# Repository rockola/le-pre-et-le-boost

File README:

# le-pre-et-le-boost
PCB for SMD FET preamp OR booster

* v0.1: initial import, unverified

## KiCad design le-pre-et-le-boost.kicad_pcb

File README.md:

# le-pre-et-le-boost
PCB for SMD FET preamp AND/OR BJT booster

* v0.1: initial import
* v0.2: THT footprints for C1/C2
* v0.3: separate in/out for both sides (for simultaneous use)

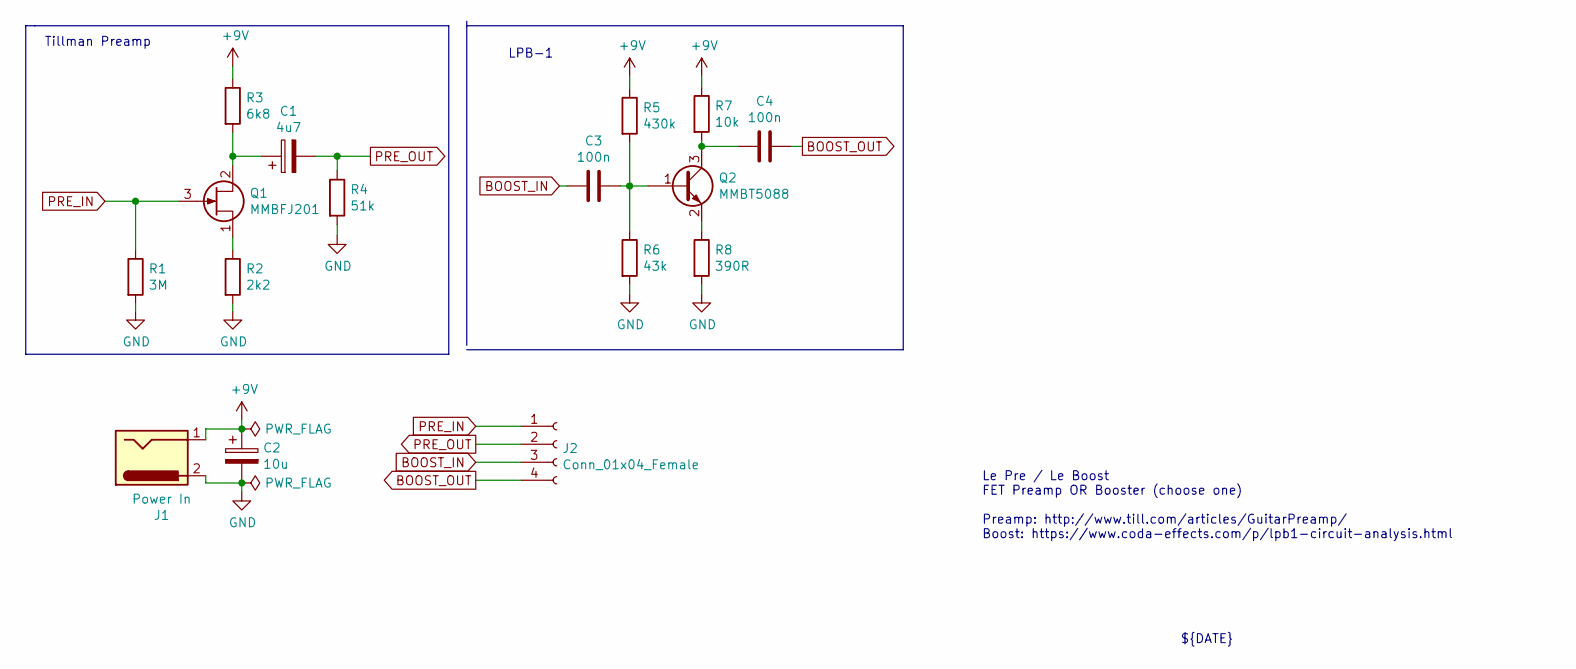
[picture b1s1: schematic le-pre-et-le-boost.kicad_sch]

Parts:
C1: 4u7; CP_D5.0_P2.50
C2: 10u; CP_D5.0_P2.50
C3, C4: 100n; C_0805_2012Metric
J1: Power In; Power_Header_2pin_VERTICAL_ALT
J2: Conn_01x04_Female; Stomp_4pin_ALT2
Q1: MMBFJ201; SOT-23
Q2: MMBT5088; SOT-23
R1: 3M; R_0805_2012Metric
R2: 2k2; R_0805_2012Metric
R3: 6k8; R_0805_2012Metric
R4: 51k; R_0805_2012Metric
R5: 430k; R_0805_2012Metric
R6: 43k; R_0805_2012Metric
R7: 10k; R_0805_2012Metric
R8: 390R; R_0805_2012Metric

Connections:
+9V: C2.1, J1.1, R3.1, R5.1, R7.1
BOOST_IN: C3.1, J2.3
BOOST_OUT: C4.2, J2.4
GND: C2.2, J1.2, R1.2, R2.2, R4.2, R6.2, R8.2
unnamed: C1.1, Q1.2 (S), R3.2
unnamed: C3.2, Q2.1 (B), R5.2, R6.1
unnamed: C4.1, Q2.3 (C), R7.2
unnamed: Q1.1 (D), R2.1
unnamed: Q2.2 (E), R8.1
PRE_IN: J2.1, Q1.3 (G), R1.1
PRE_OUT: C1.2, J2.2, R4.1

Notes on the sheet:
${REVISION}
${DATE}
LPB-1
Le Pre / Le Boost FET Preamp OR Booster (choose one) Preamp: http://www.till.com/articles/GuitarPreamp/ Boost: https://www.coda-effects.com/p/lpb1-circuit-analysis.html
Tillman Preamp
${TITLE}

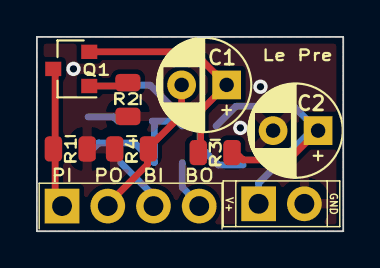
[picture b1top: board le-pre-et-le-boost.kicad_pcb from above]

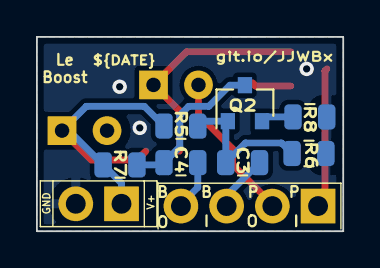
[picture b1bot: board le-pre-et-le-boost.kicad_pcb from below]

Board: 2 copper layers, 17.0 x 10.8 mm, 16 parts (7 on the bottom side), 11 nets.

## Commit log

2020-07-21 git ignores
2020-07-21 v0.1: initial import
2020-07-21 git.io URL on back silkscreen
2020-07-21 initial Gerbers
2020-07-21 Gerber preview from Oshpark
2020-07-21 initial README
2020-07-21 markdown file has to have .md suffix
2020-07-22 some position and silkscreen adjustments
2020-08-31 ground fill now specified as single zone applying to both sides
2020-08-31 v0.2: THT footprints for electrolytics
2020-08-31 v0.3: separate in/out for both sides
2020-08-31 schematic screenshot
2022-01-11 updated to KiCad 6.0
